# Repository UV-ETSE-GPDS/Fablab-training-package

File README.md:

# Fablab-training-package
The set of materials for the April training session

The folder Thermostat contains the schematics for the Main board and Sensor board.

The pinout of the used ESP12-E module is in the esp12e-pinout.png. Please note that the NodeMCU gpio numbering does not match with the original pinout, look at the https://nodemcu.readthedocs.io/en/master/en/modules/gpio/ for detailed description.

The code is in the init.lua file. It requires NodeMCU firmware v1.0 or higher with modules: adc, gpio, file, net,node,timer,wifi 

All copyright of the included materials belongs to the original authors.

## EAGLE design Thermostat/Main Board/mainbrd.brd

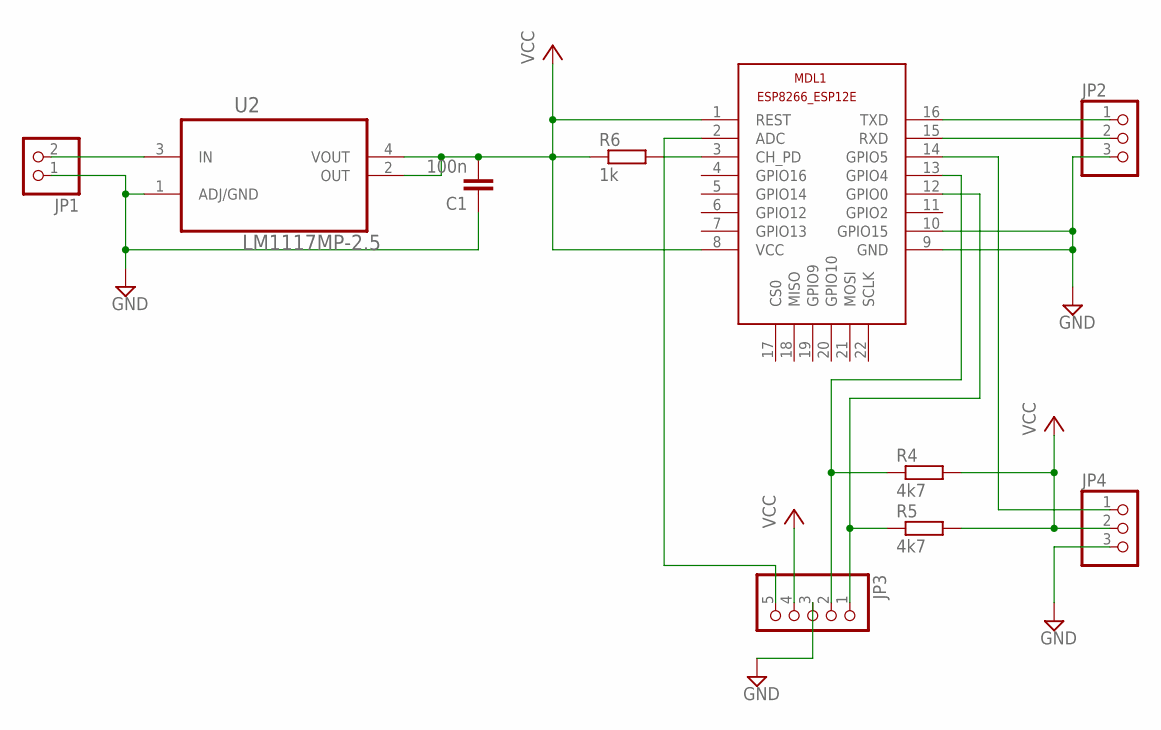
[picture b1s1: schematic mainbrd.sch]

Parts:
C1: 100n; C0805
JP1: PINHD-1X2; 1X02
JP2, JP4: PINHD-1X3; 1X03
JP3: PINHD-1X5; 1X05
MDL1: ESP8266-12EESP8266-ESP12E; ESP8266-ESP12E
R4, R5: 4k7; R0805
R6: 1k; R0805
U2: LM1117MP-2.5; SOT230P696X180-4N

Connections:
GND: C1.1, JP1.1, JP2.3, JP3.3, JP4.3, MDL1.9 (GND), MDL1.10 (GPIO15), U2.1 (ADJ/GND)
unnamed: JP2.1, MDL1.16 (TXD)
unnamed: JP2.2, MDL1.15 (RXD)
unnamed: MDL1.3 (CH_PD), R6.2
unnamed: JP1.2, U2.3 (IN)
unnamed: JP3.1, MDL1.12 (GPIO0), R5.1
unnamed: JP3.2, MDL1.13 (GPIO4), R4.1
unnamed: JP3.5, MDL1.2 (ADC)
unnamed: JP4.1, MDL1.14 (GPIO5)
VCC: C1.2, JP3.4, JP4.2, MDL1.1 (REST), MDL1.8 (VCC), R4.2, R5.2, R6.1, U2.2 (OUT), U2.4 (VOUT)

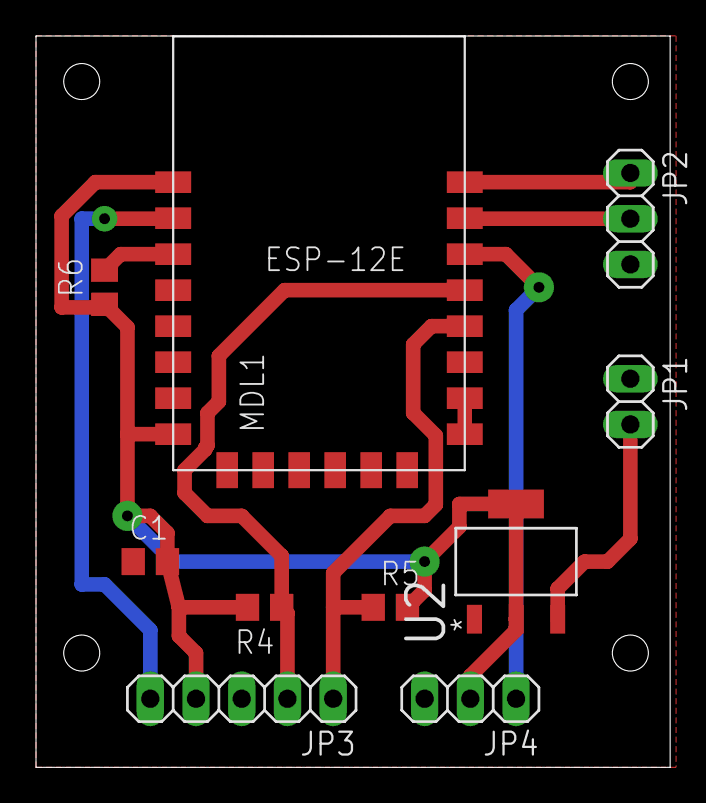
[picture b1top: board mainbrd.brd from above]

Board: 2 copper layers, 35.2 x 40.6 mm, 10 parts (0 on the bottom side), 10 nets.

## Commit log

2017-04-07 Eagle files update
2017-04-07 Added presentation about BLE
2017-04-07 Added presentations from first day.
